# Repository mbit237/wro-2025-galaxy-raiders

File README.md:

# wro-2025-galaxy-raiders -- solution summary

This repository contains the full stack for the robot: electronics (PCB design and fabrication artifacts), sensors (2D LiDAR, gyro, wheel encoders, compass), decision logic (landmark-based localisation and odometry that are fused using a complementary filter), navigation (path planning, proportional steering), colour detection for the Obstacle Challenge (Raspberry Pi Camera–based colour blob detection for green and red), and a set of utilities for calibration, plotting, as well as testing.

It is implemented in Python and designed to run on a Raspberry Pi 4b which is the primary controller. The Pi interfaces directly with the sensors (LiDAR via serial/USB, MPU6050 gyro via I²C, wheel encoders via GPIO), and controls the navigation (continuous DC drive through a motor driver; steering via a PWM-controlled servo). The custom PCB consolidates power distribution, connectors, and signal routing. 

During the run, the program reads initial ranges to estimate the robot’s start pose, continuously merges odometry with landmark corrections, follows the active path, and stops automatically once a path-segment counter reaches the configured limit.

**PCB (wro-pcb-v2 folder)**
Contains everything needed to fabricate and assemble the controller board:
Schematic & PCB: Source files for the custom board (signal routing for power in, motor driver, servo PWM, I²C, UART/USB headers for sensors, encoder inputs).
Drill / CAM: Drill files and drill G-code for CNC milling; SVGs of the board outline and copper to be milled with LaserWeb 
Connected components
Power: Battery input (screw terminal), voltage regulator for motor driver, and servo.
Actuators: Screw terminals/headers to the motor driver output and a 3-pin servo header (GND, +5/6V BEC, PWM).
Sensors: I²C header for MPU6050; UART header for LiDAR; encoder inputs to GPIO connectors.
Tactile button input to GPIO for initialisation 

**Localisation using sensors:**
coind4: functions for current lidar, parsing in each data frame and checking the checksum 
gyro.py (mpu6050): basic functions for gyro to update heading
gyro_calibration_saver.py: saves the gyro calibration readings 
[unused] lds02rr.py: functions for previous lidar, also pareses in each data frame and checks the checksum
[unused] compass.py: functions for compass module to read its heading, not implemented in current version

**Navigation**
spike.py: functions to match to lidar points to landmarks 
estimate_pose.py: functions for odometry, which uses wheel rotation and gyro to estimate the robot's position and heading while it is running. New estimate_pose function uses vectors
drive.py: navigation functions 
step_count: receive signals from encoder to calculate number of steps after a certain period of time 
steering_p: driving servo motor with pwm signal that is derived from the direction in degrees
navigation.py: functions to augment robot’s paths and drive to the path which utilises proportional control to avoid steering off path

**Obstacle Challenge**
Using camera to identify the position of the red and green blocks to know which path to take at each decision point, ie after the turn at each corner
rpicam.py: functions for detection of red and green blobs based on HSV thresholds using opencv
rpicam_calibration.py: tool to calibrate HSV thresholds for different colours with sliders using opencv

**main.py:**
specify the variables and constants: filter ratios for spike and odometry, paths for the different challenges / scenarios 
get the initial position of the robot by checking the distance away from the walls
merging the positions derived from odometry and spike using complementary filter 
while loop that checks whether the path count has reached the limit to stop the programme automatically

**Miscellaneous / Testing**
motor wiring.avif: wiring for the encoder 
button.py: activate the code when button pressed 
Plotting using sockets
client_raspi.py: functions for the raspberry pi to send the lidar points to the computer for plotting 
server_comp.py: receive lidars points to plot, switch between cartesian or polar plot 
main_plotting.py: for debugging socket code

**Uploading and debugging code:**
set up ssh in raspberry pi
Log in using [username]@ipaddress, [password]
Upload code by typing:
scp C:\[file directory]\*.py [username]@ipaddres:/[file directory]
(*.py uploads python files only as the github repository has non-python files)

**Laser cutting/ 3D printing files:**
Onshape CAD: Chassis, brackets, camera/servo mounts, etc.
https://cad.onshape.com/documents?resourceType=resourceuserowner&nodeId=66495b1552a5e72f9db8f36a
Files named “[Date] Design": contain the updates made to the chassis of the car before the final design. They also contain designs for the Ackermann steering linkages, which ensure that the inner front wheel steers at a larger angle than the outer front wheel when the car turns
“Lidar measurements”: used for simpler visualisation of the first version of the initial_pose(), which calculates the car’s starting position and if it is on the left or right side of the map.
“Pcb spacer”: 3d designs to ensure that the pcb remains balanced and does not tip over which could potentially affect connections between the pcb and raspberrypi
“Camera mount”: 3d camera mounts which point the camera at a certain angle
“Differential plate”: helps to lower the axle of the rear wheels to match the level of the motor
“Lidar mount”: plate that secures the lidar sensor to the upper chassis of the car

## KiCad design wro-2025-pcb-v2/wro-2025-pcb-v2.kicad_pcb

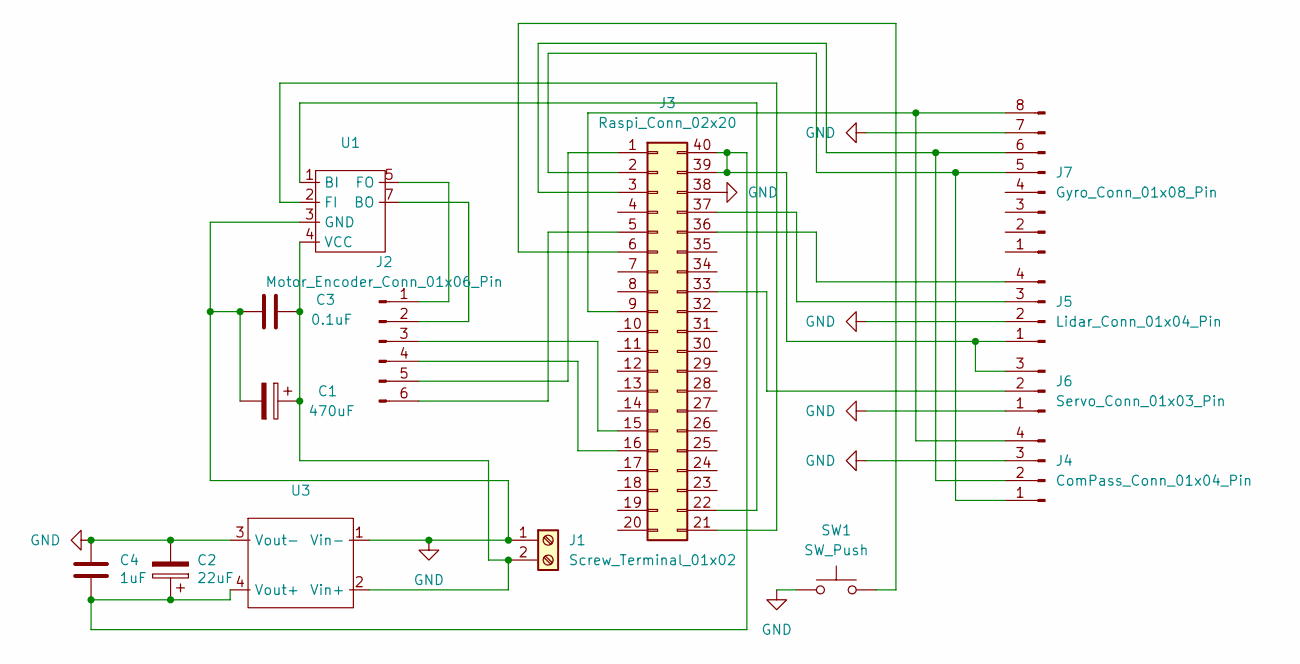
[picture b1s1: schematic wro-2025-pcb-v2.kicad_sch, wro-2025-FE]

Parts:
C1: 470uF; CP_Radial_D10.0mm_P5.00mm
C2: 22uF; CP_Radial_D5.0mm_P2.50mm
C3: 0.1uF; C_Disc_D4.3mm_W1.9mm_P5.00mm
C4: 1uF; C_Disc_D4.3mm_W1.9mm_P5.00mm
J1: Screw_Terminal_01x02; TerminalBlock_TE_282834-2_1x02_P5.08mm_Horizontal
J2: Motor_Encoder_Conn_01x06_Pin; PinHeader_1x06_P2.54mm_Vertical
J3: Raspi_Conn_02x20; PinHeader_2x20_P2.54mm_Vertical_SMD
J4: ComPass_Conn_01x04_Pin; PinHeader_1x04_P2.54mm_Vertical
J5: Lidar_Conn_01x04_Pin; PinHeader_1x04_P2.54mm_Vertical
J6: Servo_Conn_01x03_Pin; PinHeader_1x03_P2.54mm_Vertical
J7: Gyro_Conn_01x08_Pin; PinHeader_1x08_P2.54mm_Vertical
SW1: SW_Push; Tact_Switch_TL59AF160Q_E-Switch
U1: DIP-8_W7.62mm
U3: Voltage_Regulator_MP1584

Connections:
GND: C1.2, C2.2, C3.1, C4.1, J1.1, J3.24, J3.26, J3.31, J3.38, J4.3, J5.2, J6.1, J7.7, SW1.1, U1.3 (GND), U3.1 (Vin-), U3.3 (Vout-), U3.5, U3.7
unnamed: C1.1, C3.2, J1.2, U1.4 (VCC), U3.2 (Vin+), U3.6
unnamed: J2.1, U1.5 (FO)
unnamed: J2.2, U1.7 (BO)
unnamed: J2.3, J3.15
unnamed: J2.4, J3.16
unnamed: J2.5, J3.1
unnamed: J2.6, J3.5
unnamed: J3.2, J4.1, J7.5
unnamed: J3.3, J4.2, J7.6
unnamed: J3.6, SW1.2
unnamed: J3.9, J4.4, J7.8
unnamed: J3.21, U1.2 (FI)
unnamed: J3.22, U1.1 (BI)
unnamed: J3.33, J6.2
unnamed: J3.36, J5.4
unnamed: J3.37, J5.3
unnamed: C2.1, C4.2, J3.39, J3.40, J5.1, J6.3, U3.4 (Vout+), U3.8

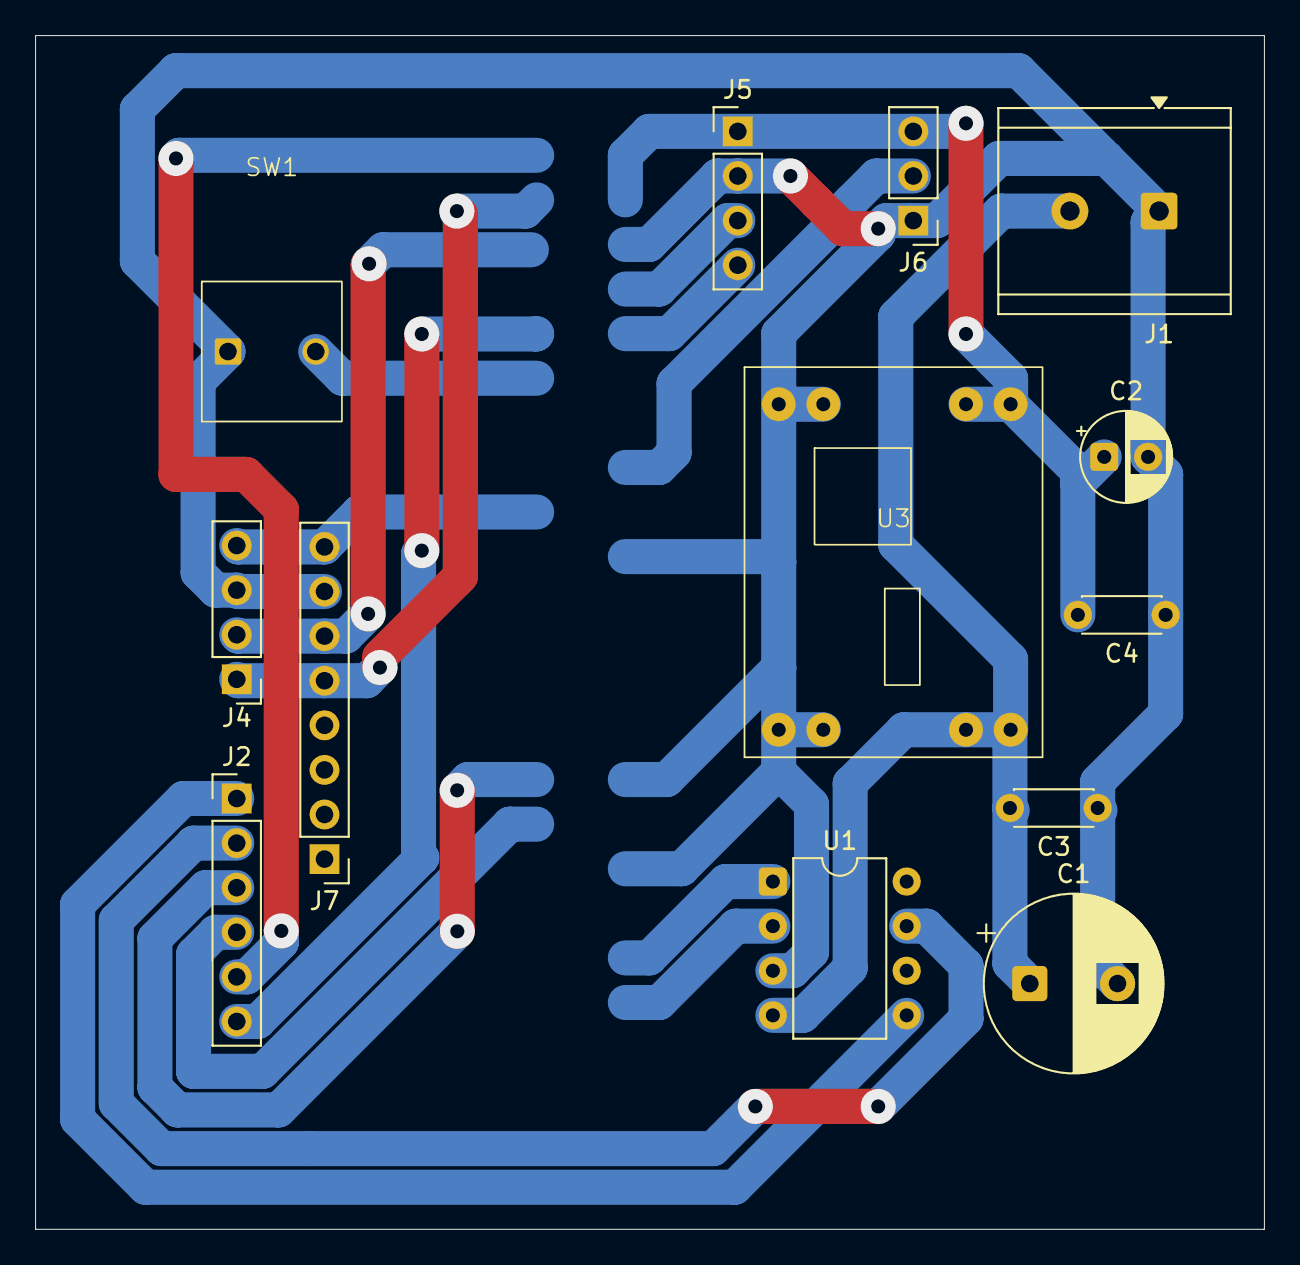
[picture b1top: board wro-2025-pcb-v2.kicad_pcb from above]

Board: 2 copper layers, 70.0 x 68.0 mm, 14 parts (1 on the bottom side), 18 nets.

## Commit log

2025-03-01 Create LICENSE
2025-03-16 Add motor-withencoder-wiring-file.avif
2025-03-16 Create docs.md
    To create a file with all the relevant links to the documents / resources
2025-04-13 initial-commit: added main.py
2025-04-13 added gyro using smbus
2025-04-20 added compass
2025-04-27 add steering function
2025-05-04 added lidar but could not read successfully
2025-05-11 finished lidar
2025-05-18 removed pi argument from lidar
2025-05-18 add new lidar coind4
2025-05-25 testing motor
2025-06-01 added socket programme
2025-06-01 camera calibration for webcam and raspberrypi
2025-06-01 plotting lidar (failed)
2025-06-03 Fixed plotting of lidar points
2025-06-08 added spike.py for spike detection, removed uart arg in CoinD4 __init__,
2025-06-08 added gyro calibration save
2025-06-13 added code to estimate pose of robot, changed gyro calibration time to 10 secs, duplicated main code to test gyro calibration
2025-06-13 Plot matches on a cartesian plane using socket
2025-06-13 added limit of -360/360, worked on navigation code
2025-06-15 added initial_pose() to determine starting position
2025-06-15 imported time in est. pose, made navigation a .py file
2025-06-15 minor fixes in estimate pose
2025-06-15 minor changes in estimate_pose.py
2025-06-15 minor changes in navigation.py
2025-06-15 changed PATH_GAIN in navigation.py
2025-06-15 added code for driving paths
2025-06-15 changed step_count to drive.steps in estimate_pose
2025-06-21 tweaked initial_pose() in main.py to check for spikes
2025-06-21 comments to explain code
2025-06-22 minor changes in main.py
2025-06-22 minor edits for comments
2025-06-22 changed initial pose function to deduce side from detected spikes + added print x and y position
2025-06-29 test_commit
2025-06-29 changed pulse_duration in drive.py, minor fix in estimate_pose.py and gyro.py, minor fixes in main, tuned PATH_GAIN, added stop.py
2025-06-29 changed paths in main
2025-07-06 added merge_position and merge_heading to reduce drifting
2025-07-06 Add PCB files
2025-07-13 tweaked POSITION_FILTER_RATIO and HEADING_FILTER_RATIO to ensure that robot does not drift too far from the path, added difference in c_spike x, y and landmark x, y in match_landmarks for debugging
2025-07-20 revamped estimate_pose using vectors
2025-07-27 fixed estimate_pose, tweaked filter ratio
2025-08-10 update plotting of lidar
2025-08-10 gyro + navigation testing
2025-08-17 button code
2025-08-17 added new paths and landmarks for open challenge, tuned theta for estimate_pose
2025-08-17 added obstacle landmarks for obstacle challenge
2025-08-17 added obstacle challenge outer and inner paths
2025-08-17 fixed inner and outer paths for obstacle challenge
2025-08-17 added opencv detection code for red and green blobs
2025-08-24 Fixed gyro calibration and added stop
2025-08-24 added counter clockwise path
2025-08-24 deleted unnecessary files
2025-08-25 changes to README file
2025-08-26 modified formatting of readme file
2025-08-31 created copy of main.py for obstacle challenge
2025-08-31 changed hsv values for red and green detection
2025-08-31 fix threshold
2025-08-31 camera cropping
2025-08-31 added paths for obstacle challenge
2025-09-05 commented while loop in rpicam
2025-09-05 changed code to detect colour in inner and outer path for obstacle challenge
2025-09-05 fixed syntax error
2025-09-05 print statement to print colour detected for obstacle challenge
2025-09-05 commented unnecessary prints
2025-09-05 fixes for main_obstacle
2025-09-05 tweaked paths, gain for obstacles
2025-09-07 adjusted paths to have a complete round
2025-09-09 Updated button programme
2025-09-09 created shell script
2025-09-09 fixed shell programme
2025-09-09 fixed main open
2025-09-09 button stop for open challenge
2025-09-09 intialiser.sh update
2025-09-09 minor changes
2025-09-09 changes to obstacle challenge main code
2025-09-09 minior changes to obstacle code
2025-10-12 minor changes during competition
2025-10-12 added program to test lidar
2025-10-12 refactoring (untested)
2025-10-12 minor changes to lidar test code
2025-10-19 edited initialiser sh file
2025-10-19 starting on tkinter window
2025-10-19 minor changes, added drive_path_back for aligning with parking path to parallel park
2025-10-24 completed tkinter window
2025-10-26 finished data window interface
2025-10-26 changes to code to follow path back to align to parking path
2025-10-30 integrate tkinter into refactored code
2025-11-02 update interface
2025-11-02 successfully tested refactored code
2025-11-02 minor change
2025-11-02 minor changes pt 2
2025-11-02 integrated parking code in main_obstacle
2025-11-03 parking v1.0
2025-11-10 minor changes pt 3
2025-11-16 minor change pt 4
2025-11-16 path_back changes
2025-11-16 parking updated
2025-11-16 minor changes pt 5
2025-11-16 syntax error fix
2025-11-16 parking update X.X
2025-11-21 changed max steer angle to 60
2025-11-21 tuned rpicam red threshold
2025-11-22 minor changes to tune parking
2025-11-22 fixed getting into parking position with lidar
2025-11-23 ccw direction changes
2025-11-24 changes to tune obstacle and open runs
2025-11-24 MOSTLY WORKING CAN USE FOR FINALS, PLS REVERT TO THIS IF ANYTHING ELSE IN THE FUTURE FAILS
2025-11-24 STILL WORKING BUT WITH MINOR CHANGES TO FIX CERTAIN OBSTACLE SCENARIOS
2025-11-24 FINISHED TUNING OBSTACLE AND PARKING
2025-11-25 fixed socket disconnect
2025-11-25 changes to flip direction when avoiding red and green obstacles. CORRECT VERSION
2025-11-25 reverted back to button presses to start robot run
2025-11-25 adjusting readme file
2025-11-25 changed minimum spike distance for initial_pose()
2025-11-26 changes to green colour threshold
2025-11-26 FINAL last minute edits to tune parking + obstacle run
2025-11-28 Comp Day 1 changes
2025-12-01 Comp day 3 changes
